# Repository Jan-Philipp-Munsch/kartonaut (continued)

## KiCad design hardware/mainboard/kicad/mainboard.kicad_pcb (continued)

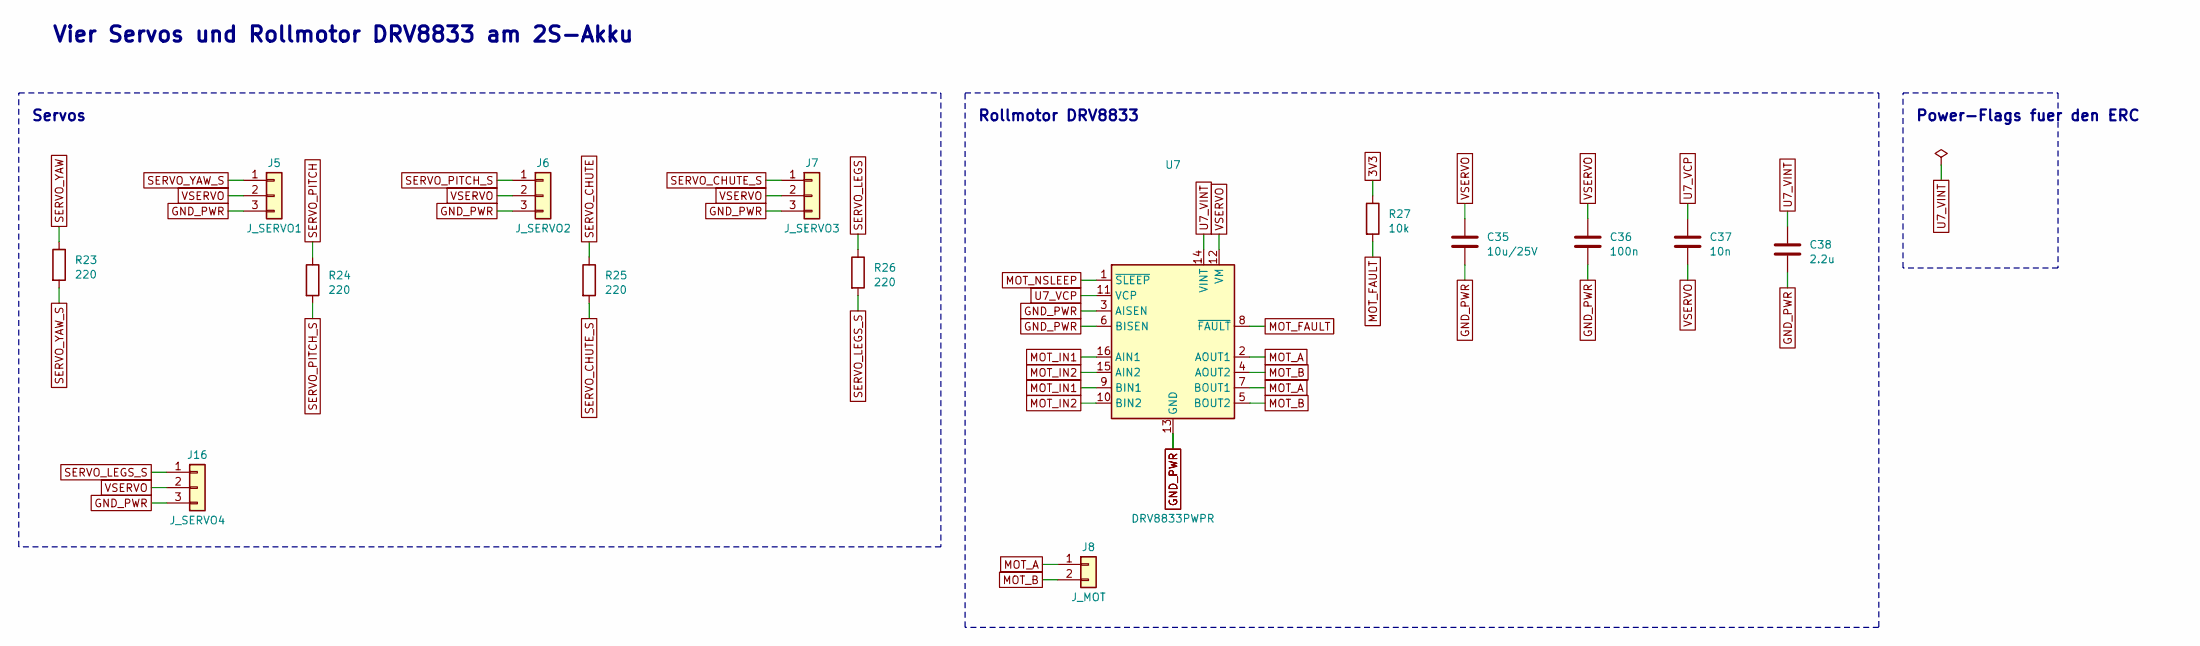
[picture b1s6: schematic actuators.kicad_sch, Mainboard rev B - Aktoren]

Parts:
C35: 10u/25V; C_0805_2012Metric
C36: 100n; C_0603_1608Metric
C37: 10n; C_0603_1608Metric
C38: 2.2u; C_0603_1608Metric
J5: J_SERVO1; JST_XH_S3B-XH-A_1x03_P2.50mm_Horizontal
J6: J_SERVO2; JST_XH_S3B-XH-A_1x03_P2.50mm_Horizontal
J7: J_SERVO3; JST_XH_B3B-XH-A_1x03_P2.50mm_Vertical
J8: J_MOT; JST_XH_B2B-XH-A_1x02_P2.50mm_Vertical
J16: J_SERVO4; JST_XH_B3B-XH-A_1x03_P2.50mm_Vertical
R23, R24, R25, R26: 220; R_0603_1608Metric
R27: 10k; R_0603_1608Metric
U7: DRV8833PWPR; HTSSOP-16-1EP_4.4x5mm_P0.65mm_EP3.4x5mm_Mask2.46x2.31mm_The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; LCSC C50506

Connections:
3V3: R27.1; also elsewhere on the board
GND_PWR: C35.2, C36.2, C38.2, J5.3, J6.3, J7.3, J16.3, U7.3 (AISEN), U7.6 (BISEN), U7.13 (GND), U7.17 (GND); also elsewhere on the board
MOT_A: J8.1, U7.2 (AOUT1), U7.7 (BOUT1)
MOT_B: J8.2, U7.4 (AOUT2), U7.5 (BOUT2)
MOT_FAULT: R27.2, U7.8 (~FAULT); also elsewhere on the board
MOT_IN1: U7.9 (BIN1), U7.16 (AIN1); also elsewhere on the board
MOT_IN2: U7.10 (BIN2), U7.15 (AIN2); also elsewhere on the board
MOT_NSLEEP: U7.1 (~SLEEP); also elsewhere on the board
SERVO_CHUTE: R25.1; also elsewhere on the board
SERVO_CHUTE_S: J7.1, R25.2
SERVO_LEGS: R26.1; also elsewhere on the board
SERVO_LEGS_S: J16.1, R26.2
SERVO_PITCH: R24.1; also elsewhere on the board
SERVO_PITCH_S: J6.1, R24.2
SERVO_YAW: R23.1; also elsewhere on the board
SERVO_YAW_S: J5.1, R23.2
U7_VCP: C37.1, U7.11 (VCP)
U7_VINT: C38.1, U7.14 (VINT)
VSERVO: C35.1, C36.1, C37.2, J5.2, J6.2, J7.2, J16.2, U7.12 (VM); also elsewhere on the board

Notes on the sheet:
Vier Servos und Rollmotor DRV8833 am 2S-Akku
Servos
Rollmotor DRV8833
Power-Flags fuer den ERC

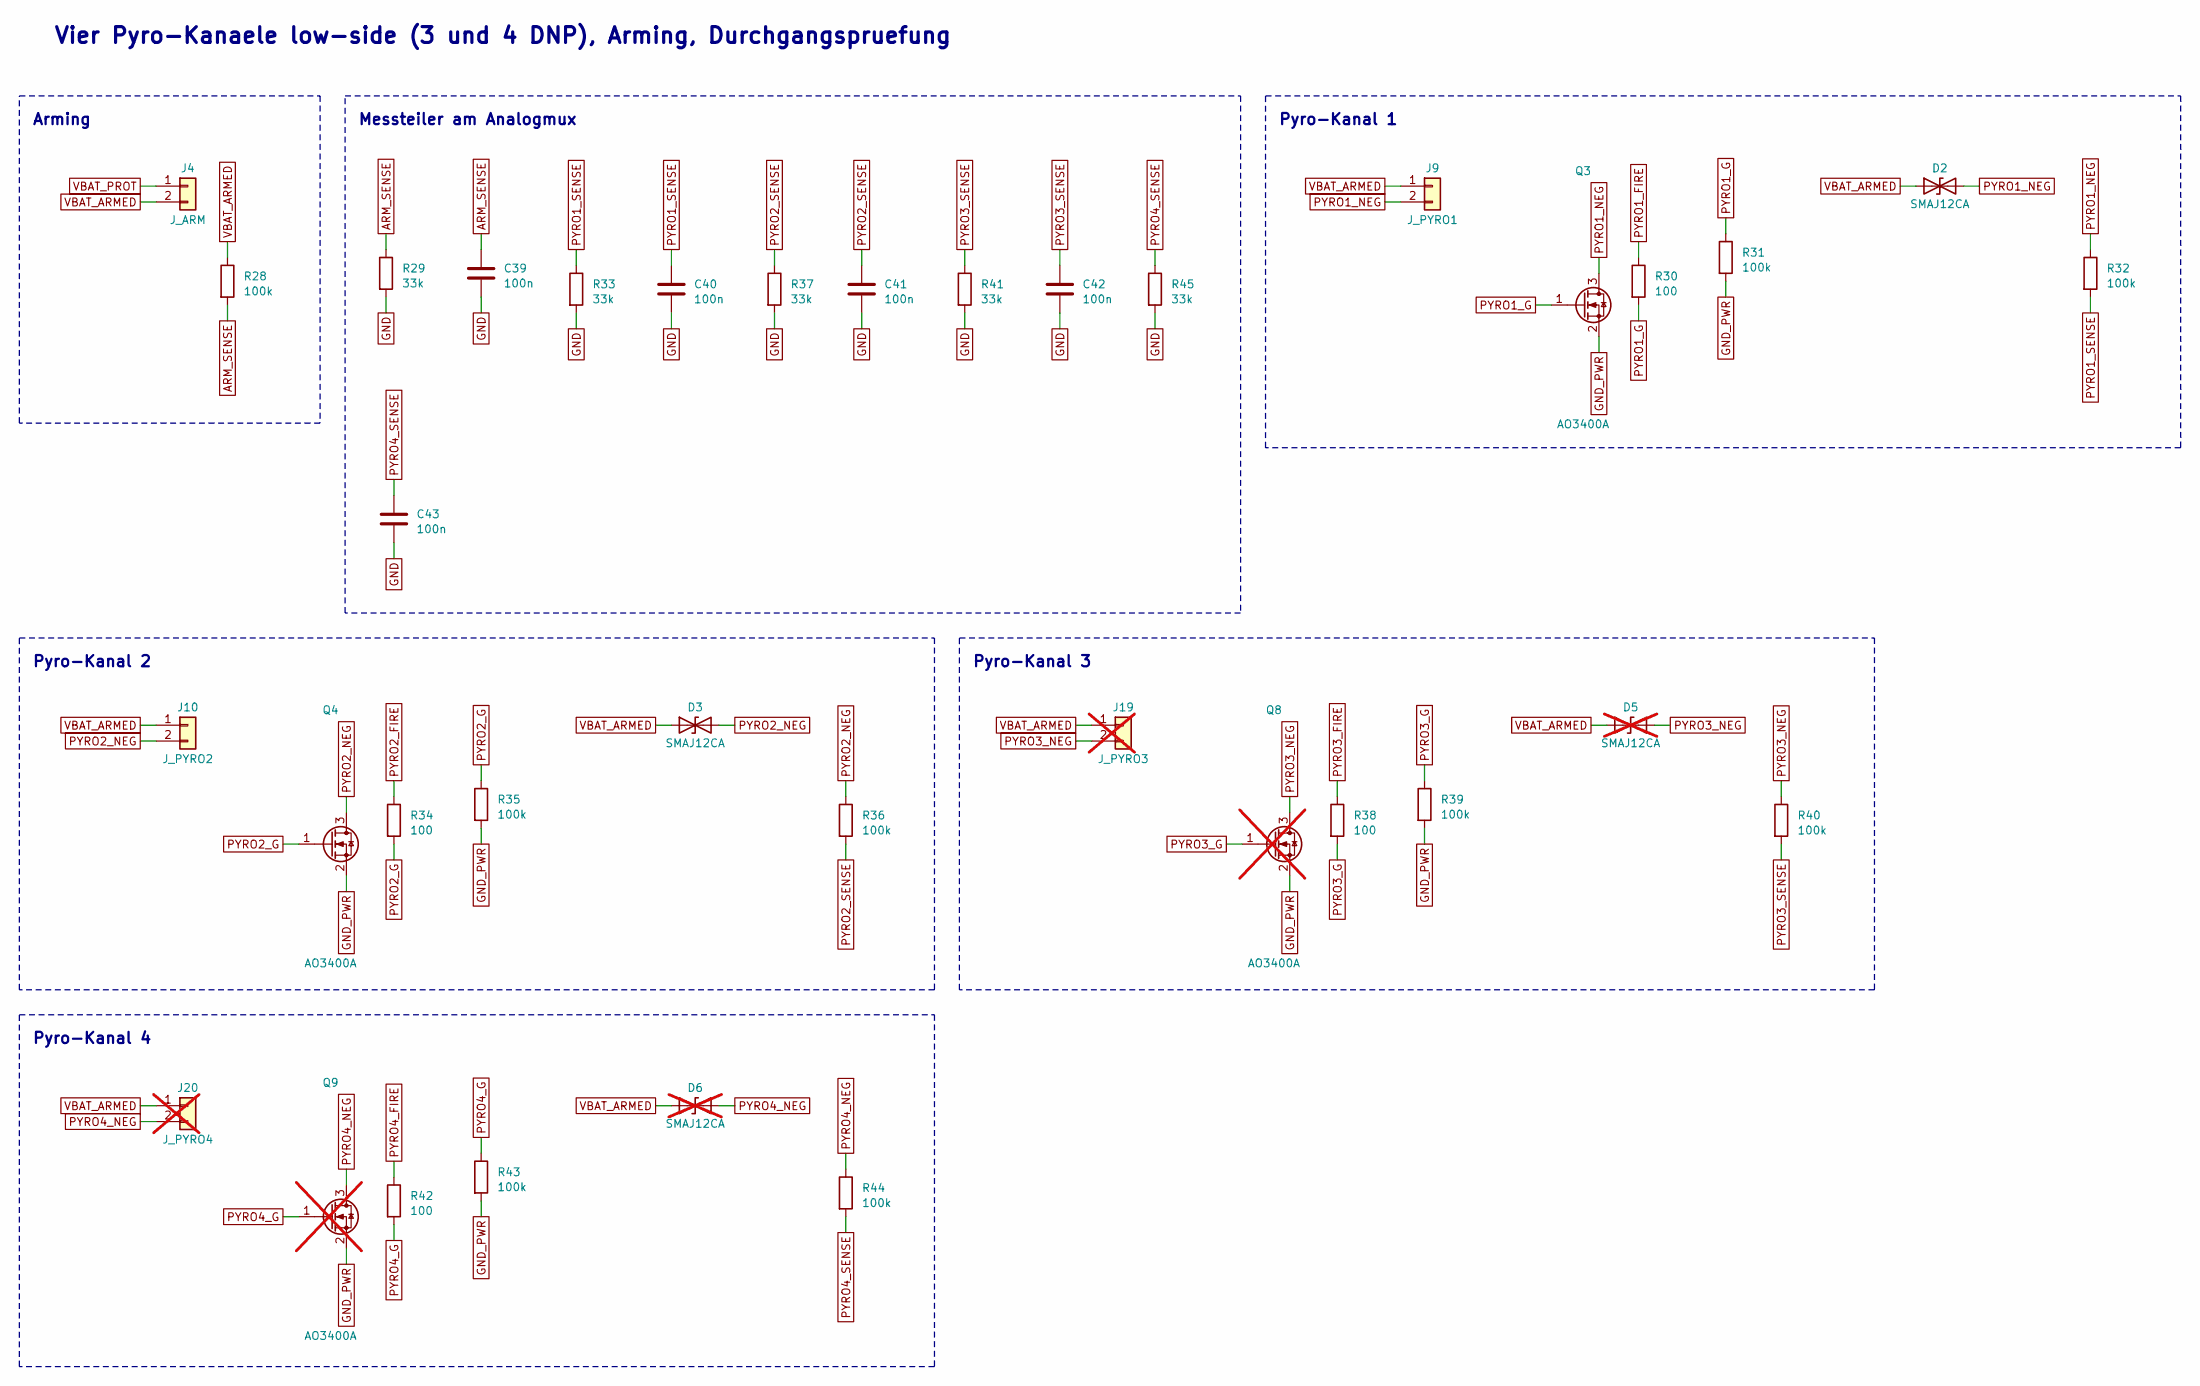
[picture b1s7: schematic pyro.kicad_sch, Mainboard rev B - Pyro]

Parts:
C39, C40, C41, C42, C43: 100n; C_0603_1608Metric
D2, D3: SMAJ12CA; D_SMA
D5, D6: SMAJ12CA; D_SMA; not fitted
J4: J_ARM; JST_XH_B2B-XH-A_1x02_P2.50mm_Vertical
J9: J_PYRO1; JST_XH_S2B-XH-A_1x02_P2.50mm_Horizontal
J10: J_PYRO2; JST_XH_S2B-XH-A_1x02_P2.50mm_Horizontal
J19: J_PYRO3; JST_XH_S2B-XH-A_1x02_P2.50mm_Horizontal; not fitted
J20: J_PYRO4; JST_XH_S2B-XH-A_1x02_P2.50mm_Horizontal; not fitted
Q3, Q4: AO3400A; SOT-23; LCSC C20917
Q8, Q9: AO3400A; SOT-23; LCSC C20917; not fitted
R28, R31, R32, R35, R36, R39, R40, R43, R44: 100k; R_0603_1608Metric
R29, R33, R37, R41, R45: 33k; R_0603_1608Metric
R30, R34, R38, R42: 100; R_0603_1608Metric

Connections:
ARM_SENSE: C39.1, R28.2, R29.1; also elsewhere on the board
GND: C39.2, C40.2, C41.2, C42.2, C43.2, R29.2, R33.2, R37.2, R41.2, R45.2; also elsewhere on the board
GND_PWR: Q3.2 (S), Q4.2 (S), Q8.2 (S), Q9.2 (S), R31.2, R35.2, R39.2, R43.2; also elsewhere on the board
PYRO1_FIRE: R30.1; also elsewhere on the board
PYRO1_G: Q3.1 (G), R30.2, R31.1
PYRO1_NEG: D2.2 (A2), J9.2, Q3.3 (D), R32.1
PYRO1_SENSE: C40.1, R32.2, R33.1; also elsewhere on the board
PYRO2_FIRE: R34.1; also elsewhere on the board
PYRO2_G: Q4.1 (G), R34.2, R35.1
PYRO2_NEG: D3.2 (A2), J10.2, Q4.3 (D), R36.1
PYRO2_SENSE: C41.1, R36.2, R37.1; also elsewhere on the board
PYRO3_FIRE: R38.1; also elsewhere on the board
PYRO3_G: Q8.1 (G), R38.2, R39.1
PYRO3_NEG: D5.2 (A2), J19.2, Q8.3 (D), R40.1
PYRO3_SENSE: C42.1, R40.2, R41.1; also elsewhere on the board
PYRO4_FIRE: R42.1; also elsewhere on the board
PYRO4_G: Q9.1 (G), R42.2, R43.1
PYRO4_NEG: D6.2 (A2), J20.2, Q9.3 (D), R44.1
PYRO4_SENSE: C43.1, R44.2, R45.1; also elsewhere on the board
VBAT_ARMED: D2.1 (A1), D3.1 (A1), D5.1 (A1), D6.1 (A1), J4.2, J9.1, J10.1, J19.1, J20.1, R28.1
VBAT_PROT: J4.1; also elsewhere on the board

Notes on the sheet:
Vier Pyro-Kanaele low-side (3 und 4 DNP), Arming, Durchgangspruefung
Arming
Messteiler am Analogmux
Pyro-Kanal 1
Pyro-Kanal 2
Pyro-Kanal 3
Pyro-Kanal 4

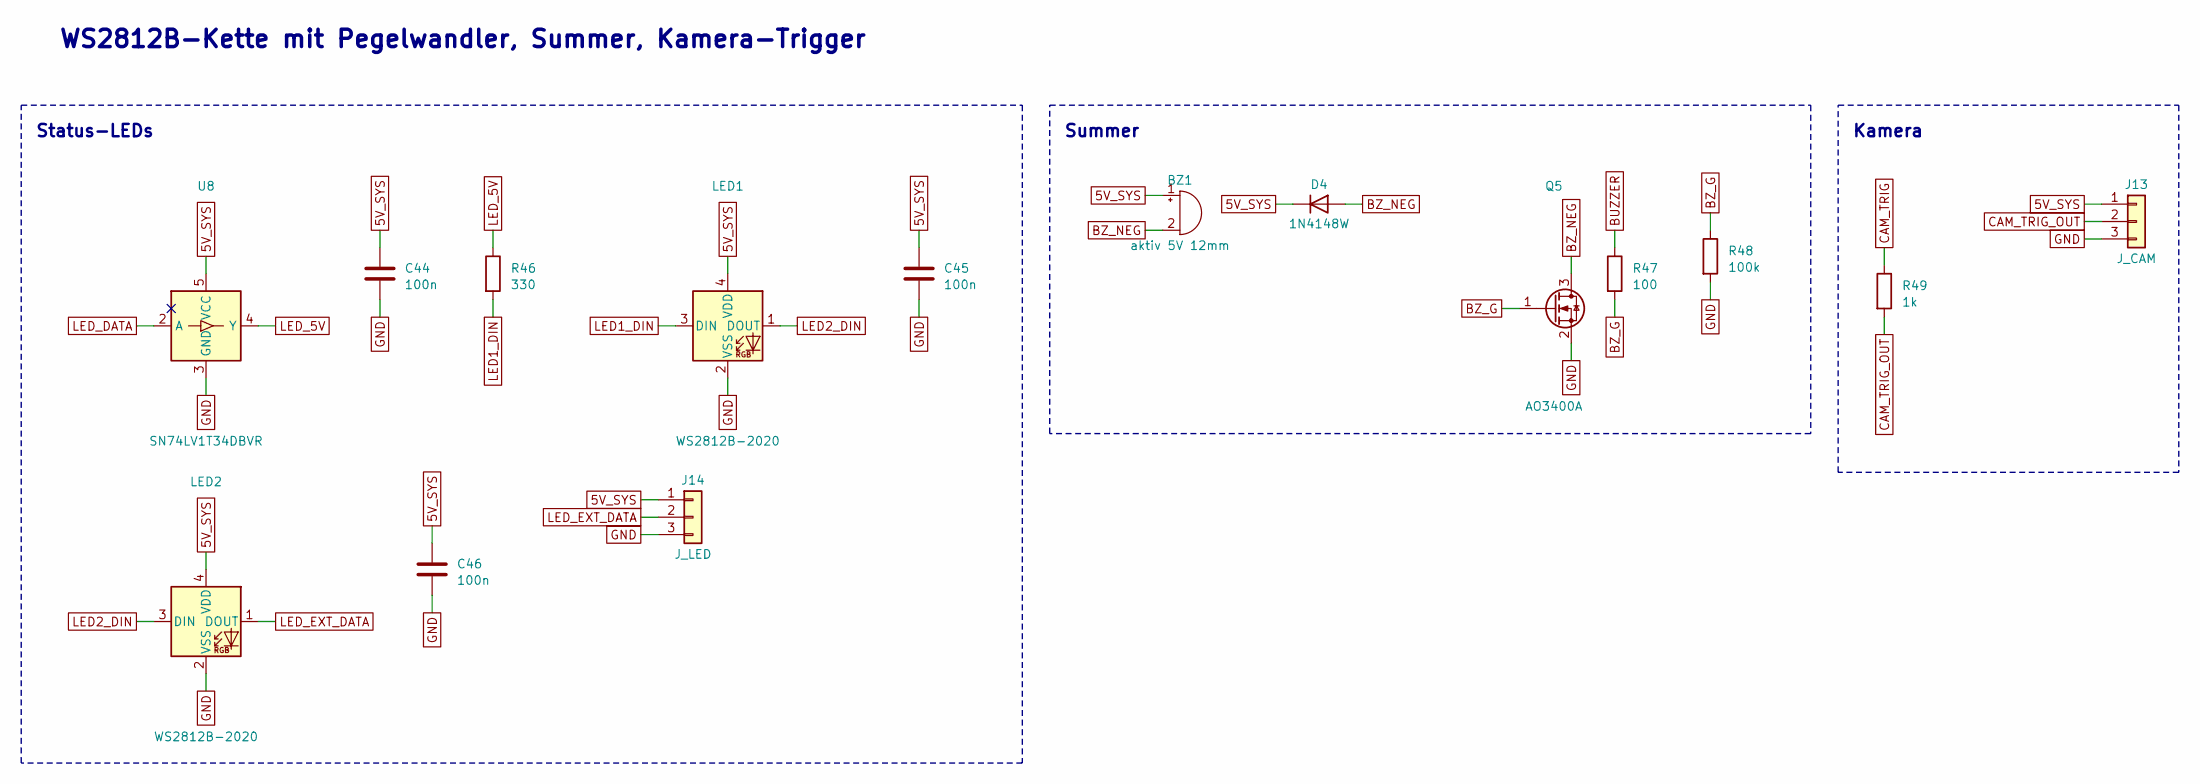
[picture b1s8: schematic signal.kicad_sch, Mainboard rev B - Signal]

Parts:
BZ1: aktiv 5V 12mm; Buzzer_12x9.5RM7.6
C44, C45, C46: 100n; C_0603_1608Metric
D4: 1N4148W; D_SOD-123; LCSC C81598
J13: J_CAM; JST_GH_BM03B-GHS-TBT_1x03-1MP_P1.25mm_Vertical
J14: J_LED; JST_GH_BM03B-GHS-TBT_1x03-1MP_P1.25mm_Vertical
LED1, LED2: WS2812B-2020; LED_WS2812B-2020_PLCC4_2.0x2.0mm; LCSC C965555
Q5: AO3400A; SOT-23; LCSC C20917
R46: 330; R_0603_1608Metric
R47: 100; R_0603_1608Metric
R48: 100k; R_0603_1608Metric
R49: 1k; R_0603_1608Metric
U8: SN74LV1T34DBVR; SOT-23-5

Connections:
5V_SYS: BZ1.1 (+), C44.1, C45.1, C46.1, D4.1 (K), J13.1, J14.1, LED1.4 (VDD), LED2.4 (VDD), U8.5 (VCC); also elsewhere on the board
BUZZER: R47.1; also elsewhere on the board
BZ_G: Q5.1 (G), R47.2, R48.1
BZ_NEG: BZ1.2 (-), D4.2 (A), Q5.3 (D)
CAM_TRIG: R49.1; also elsewhere on the board
CAM_TRIG_OUT: J13.2, R49.2
GND: C44.2, C45.2, C46.2, J13.3, J14.3, LED1.2 (VSS), LED2.2 (VSS), Q5.2 (S), R48.2, U8.3 (GND); also elsewhere on the board
LED1_DIN: LED1.3 (DIN), R46.2
LED2_DIN: LED1.1 (DOUT), LED2.3 (DIN)
LED_5V: R46.1, U8.4 (Y)
LED_DATA: U8.2 (A); also elsewhere on the board
LED_EXT_DATA: J14.2, LED2.1 (DOUT)

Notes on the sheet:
WS2812B-Kette mit Pegelwandler, Summer, Kamera-Trigger
Status-LEDs
Summer
Kamera

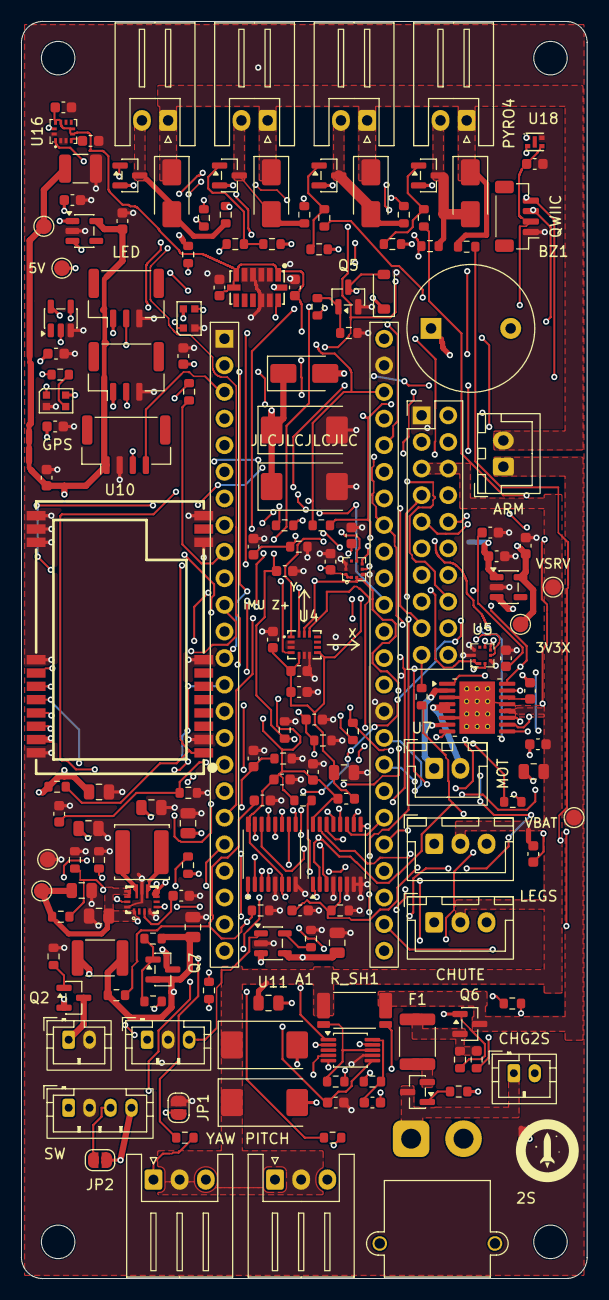
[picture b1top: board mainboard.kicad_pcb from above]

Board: 4 copper layers, 54.0 x 120.0 mm, 174 parts (0 on the bottom side), 117 nets.

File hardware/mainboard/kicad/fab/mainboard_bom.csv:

Comment,Designator,Footprint,LCSC Part #
100n,"C1,C2,C3,C7,C12,C24,C25,C26,C29,C30,C34,C36,C39,C40,C41,C42,C43,C44,C45,C46,C47,C48,C49",C_0603_1608Metric,
330u/16V polymer,"C4,C5",CP_EIA-7343-31_Kemet-D,
10u/25V,"C6,C10,C11,C35",C_0805_2012Metric,
4.7u,"C8,C9",C_0805_2012Metric,
22u/10V,"C13,C14,C15",C_0805_2012Metric,
470u/6.3V polymer,"C16,C17",CP_EIA-7343-31_Kemet-D,
1u,"C18,C19,C21,C22",C_0603_1608Metric,
100u/6.3V,C20,C_1210_3225Metric,
10u,"C23,C33",C_0805_2012Metric,
2.2u,"C27,C38",C_0603_1608Metric,
10n,"C28,C37",C_0603_1608Metric,
SS14,D1,D_SMA,C2480
SMAJ12CA,"D2,D3",D_SMA,
1N4148W,D4,D_SOD-123,C81598
3A hold 6A trip,F1,Fuse_1812_4532Metric,
2A hold,F2,Fuse_1812_4532Metric,
600R@100MHz,FB1,L_0603_1608Metric,
J_GPS,J11,JST_GH_BM04B-GHS-TBT_1x04-1MP_P1.25mm_Vertical,
J_QWIIC,J12,JST_SH_BM04B-SRSS-TB_1x04-1MP_P1.00mm_Vertical,
J_CAM,J13,JST_GH_BM03B-GHS-TBT_1x03-1MP_P1.25mm_Vertical,
J_LED,J14,JST_GH_BM03B-GHS-TBT_1x03-1MP_P1.25mm_Vertical,
1.5u Isat>=4A,L2,L_Changjiang_FNR5040S,
WS2812B-2020,"LED1,LED2",LED_WS2812B-2020_PLCC4_2.0x2.0mm,C965555
AO3401A,"Q1,Q2,Q6,Q7",SOT-23,C15127
AO3400A,"Q3,Q4,Q5",SOT-23,C20917
10k,"R1,R8,R18,R19,R22,R27",R_0603_1608Metric,
100k,"R2,R4,R9,R11,R28,R31,R32,R35,R36,R39,R40,R43,R44,R48",R_0603_1608Metric,
1k,"R3,R10,R49",R_0603_1608Metric,
33k,"R5,R12,R29,R33,R37,R41,R45",R_0603_1608Metric,
10,"R6,R7",R_0603_1608Metric,
2k,R13,R_0603_1608Metric,
680k,R14,R_0603_1608Metric,
130k,R15,R_0603_1608Metric,
330k,R16,R_0603_1608Metric,
115k,R17,R_0603_1608Metric,
4.7k,"R20,R21",R_0603_1608Metric,
220,"R23,R24,R25,R26",R_0603_1608Metric,
100,"R30,R34,R38,R42,R47",R_0603_1608Metric,
330,R46,R_0603_1608Metric,
20m 1% 1W,R_SH1,R_2512_Kelvin,
TPS63070RNMR,U2,VQFN-15_L3.0-W2.5-P0.50-BL,C109322
AP2112K-3.3TRG1,"U3,U14",SOT-23-5,C51118
LSM6DSV16X,U4,LGA-14_L3.0-W2.5-P0.50-TL,C5267406
BMP390,U5,LGA-10_L2.0-W2.0-P0.50-BL,C5124834
INA239AIDGSR,U6,MSOP-10_3x3mm_P0.5mm,
DRV8833PWPR,U7,HTSSOP-16-1EP_4.4x5mm_P0.65mm_EP3.4x5mm_Mask2.46x2.31mm_ThermalVias,C50506
SN74LV1T34DBVR,U8,SOT-23-5,
E22-400T22S,U10,WIRELM-SMD_E22-400T22S_1,C2903765
MCP73831T-2ACI/OT,U11,SOT-23-5,C424093
74HC138PW,U12,TSSOP-16_4.4x5mm_P0.65mm,
74HC4051PW,U13,TSSOP-16_4.4x5mm_P0.65mm,
LIS3MDL,U16,LGA-12_L2.0-W2.0-P0.50-BL,C478483
SHT40-AD1B,U18,DFN-4_L1.5-W1.5-P0.8-TL-EP,C2848306

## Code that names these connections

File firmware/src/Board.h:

#pragma once
// Board.h – Welche Hardware trägt die Flug-Firmware?
//
// Zwei Rückenden, gewählt über die Build-Variable BOARD_REVB (platformio.ini):
//
//   (ohne)       Breakouts am Teensy 4.1 mit Dupont-Kabeln: ICM-20948 (I²C, DMP),
//                BMP280, INA219, HC-12 an Serial8, zwei WS2812B an Pin 5 und 6.
//                Pins wie bisher in Config.h.
//   BOARD_REVB   Mainboard rev B: ICM-42688-P, BMP390, INA239 an SPI1 über den
//                CS-Decoder, Akkus/ARM/Pyro-Durchgang über die Analogmux, LoRa
//                E22 an Serial8, LED-Kette an Pin 5. Pins aus lib/mainboard_revb/
//                BoardRevB.h, geprüft durch firmware/tools/check_board_pins.py.
//
// Die Module (Sensors, Control, Indicators, Radio, Pyro-Ausgänge) lesen Pins
// nur von hier. Config.h hält Physik, Gewinne und Schalter, nichts Elektrisches.
#include <Arduino.h>
#include "MathTypes.h"

#ifdef BOARD_REVB
  #include "BoardRevB.h"
  #define BOARD_NAME "Mainboard rev B"

  constexpr int PIN_BEEPER      = revb::PIN_BUZZER;       // 37
  constexpr int PIN_LED_DATA    = revb::PIN_LED_DATA;     // 5, Kette LED1 -> LED2 -> J_LED
  constexpr int LED_COUNT       = revb::LED_COUNT_ONBOARD;
  constexpr int PIN_MOT_IN1     = revb::PIN_MOT_IN1;
  constexpr int PIN_MOT_IN2     = revb::PIN_MOT_IN2;
  constexpr int PIN_MOT_NSLEEP  = revb::PIN_MOT_NSLEEP;   // DRV8833, tief = Motor stromlos
  constexpr int PIN_MOT_FAULT   = revb::PIN_MOT_FAULT;
  constexpr int PIN_SERVO_YAW   = revb::PIN_SERVO_YAW;
  constexpr int PIN_SERVO_PITCH = revb::PIN_SERVO_PITCH;
  constexpr int PIN_SERVO_CHUTE = revb::PIN_SERVO_CHUTE;
  constexpr int PIN_SERVO_LEGS  = revb::PIN_SERVO_LEGS;
  constexpr int PIN_PYRO_FIRE[4] = {revb::PIN_PYRO1_FIRE, revb::PIN_PYRO2_FIRE, revb::PIN_PYRO3_FIRE, revb::PIN_PYRO4_FIRE};
  constexpr bool PYRO_FITTED[4]  = {revb::PYRO_FITTED[0], revb::PYRO_FITTED[1], revb::PYRO_FITTED[2], revb::PYRO_FITTED[3]};
  constexpr int PIN_PYRO1       = revb::PIN_PYRO1_FIRE;
  constexpr int PIN_CAM_TRIG    = revb::PIN_CAM_TRIG;
  constexpr int PIN_THROTTLE    = revb::PIN_PWM_EXT;      // ESC am Prüfstand (J_STACK PWM_EXT)
  constexpr int PIN_LORA_M0     = revb::PIN_LORA_M0;
  constexpr int PIN_LORA_M1     = revb::PIN_LORA_M1;
  constexpr int PIN_LORA_AUX    = revb::PIN_LORA_AUX;
  constexpr int PIN_LORA_NRST   = revb::PIN_LORA_NRST;
  constexpr bool HAS_ARM_SENSE   = true;    // Schlüsselschalter messbar
  constexpr bool HAS_PYRO_SENSE  = true;    // Durchgang je Kanal messbar
  constexpr bool HAS_VBAT_SENSE  = true;    // beide Akkus am ADC
  constexpr bool HAS_GPS         = true;    // J_GPS an Serial1
  constexpr bool RADIO_IS_E22    = true;

  // Drehung Chip -> Körpersystem (x, y quer, z Rollachse zur Spitze).
  // Spezifikation rev B §2: Chip X zeigt quer (+u), Chip Y zur Spitze (+v),
  // also Körper = (c.x, -c.z, c.y). TODO: nach der endgültigen Platzierung von
  // U4 (Bestückungsdruck-Pfeile) am Gerät prüfen: Spitze nach oben -> a.z ≈ +9,81.
  inline Vec3 chipToBody(const Vec3& c) { return Vec3(c.x, -c.z, c.y); }

#else
  #define BOARD_NAME "Breakouts (Teensy 4.1, I2C)"

  constexpr int PIN_BEEPER      = 13;
  constexpr int PIN_LED1        = 5;    // WS2812B, einzeln
  constexpr int PIN_LED2        = 6;
  constexpr int LED_COUNT       = 2;
  constexpr int PIN_MOT_IN1     = 2;    // Rollmotor, H-Brücke
  constexpr int PIN_MOT_IN2     = 3;
  constexpr int PIN_MOT_NSLEEP  = -1;   // nicht vorhanden
  constexpr int PIN_MOT_FAULT   = -1;
  constexpr int PIN_SERVO_YAW   = 28;   // TVC
  constexpr int PIN_SERVO_PITCH = 29;
  constexpr int PIN_SERVO_CHUTE = 9;    // Fallschirm (Servo, Reserve)
  constexpr int PIN_SERVO_LEGS  = -1;
  constexpr int PIN_PYRO_FIRE[4] = {23, 22, -1, -1};   // Low-Side-MOSFET-Modul an 23 (Pyro-Test)
  constexpr bool PYRO_FITTED[4]  = {true, false, false, false};
  constexpr int PIN_PYRO1       = 23;
  constexpr int PIN_CAM_TRIG    = -1;
  constexpr int PIN_THROTTLE    = 10;   // ESC am Prüfstand, freier PWM-Pin
  constexpr int PIN_LORA_M0     = -1;   // HC-12: SET-Pin nicht benutzt
  constexpr int PIN_LORA_M1     = -1;
  constexpr int PIN_LORA_AUX    = -1;
  constexpr int PIN_LORA_NRST   = -1;
  constexpr bool HAS_ARM_SENSE   = false;
  constexpr bool HAS_PYRO_SENSE  = false;
  constexpr bool HAS_VBAT_SENSE  = false;
  constexpr bool HAS_GPS         = false;
  constexpr bool RADIO_IS_E22    = false;

  constexpr uint32_t I2C_MAIN_SPEED_HZ = 400000;   // BMP280, INA219, ICM-20948
  // Lage des ICM-20948-Breakouts: wie bisher (Chipachsen = Körperachsen)
  inline Vec3 chipToBody(const Vec3& c) { return c; }
#endif

// Funk hängt bei beiden an Serial8 (RX8 = 34, TX8 = 35)
#define RADIO_SERIAL Serial8
#define GPS_SERIAL   Serial1

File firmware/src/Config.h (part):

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#ifdef BOARD_REVB
// Mainboard rev B: Pins aus BoardRevB.h; hier nur die Aliase, die die Module benutzen.
constexpr int PIN_BEEPER      = 37;
constexpr int PIN_LED_DATA    = 5;    // WS2812B-Kette LED1 -> LED2
constexpr int PIN_MOT_IN1     = 2;    // DRV8833
constexpr int PIN_MOT_IN2     = 3;
constexpr int PIN_MOT_NSLEEP  = 11;
constexpr int PIN_SERVO_YAW   = 28;
constexpr int PIN_SERVO_PITCH = 29;
constexpr int PIN_SERVO_CHUTE = 9;
constexpr int PIN_PYRO1       = 23;
constexpr int PIN_PYRO2       = 22;
constexpr int PIN_RADIO_M0    = 33;   // E22: M0 = M1 = 0 -> transparenter Modus
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constexpr int PIN_BEEPER      = 13;
constexpr int PIN_LED1        = 5;    // WS2812B
constexpr int PIN_LED2        = 6;    // WS2812B
constexpr int PIN_MOT_IN1     = 2;    // Rollmotor, H-Brücke
constexpr int PIN_MOT_IN2     = 3;
constexpr int PIN_SERVO_YAW   = 28;   // TVC
constexpr int PIN_SERVO_PITCH = 29;   // TVC
constexpr int PIN_SERVO_CHUTE = 9;    // Fallschirm
constexpr int PIN_PYRO1       = 23;   // Low-Side-MOSFET, Mainboard rev A: PYRO1_FIRE
constexpr int PIN_PYRO2       = -1;   // nicht vorhanden
#endif
// Funk hängt an Serial8 (RX8 = 34, TX8 = 35): HC-12 heute, E22 auf rev B
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constexpr bool     THROTTLE_ENABLED      = false;    // erst mit Drosselmechanik und Experiment E05
constexpr float    THROTTLE_F_MIN        = 0.5f;     // Axialschub bei ganz eingeschwenkten Pads (Kennlinie E05)
#ifdef BOARD_REVB
constexpr int      PIN_SERVO_THROTTLE    = 10;       // J_SERVO4 (SERVO_LEGS) an VSERVO, solange die Beine keinen Servo haben
#else
constexpr int      PIN_SERVO_THROTTLE    = -1;       // Breakouts: kein freier Servoausgang
#endif
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constexpr uint32_t PYRO_BACKUP_DELAY_MS = 1500;    // Kanal 2 zündet so viel später, falls bestückt
constexpr uint32_t PYRO_RETRY_DELAY_MS  = 500;     // zweiter Versuch, wenn der Durchgang nach dem Puls bleibt
constexpr uint8_t  PYRO_MAX_FIRES       = 2;       // Versuche je Kanal
constexpr float    PYRO_ARM_MIN_V       = 5.0f;    // ARM_SENSE darüber = scharf (2S hinter dem Schlüssel)
constexpr float    PYRO_CONT_MIN_RATIO  = 0.8f;    // Durchgang: PYRO_SENSE > Ratio · ARM

// ===== Telemetrie (Telemetry.h) =====
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
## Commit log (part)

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2025-10-12 test
2025-10-12 test 2
2025-10-13 sd_logger, flash fail
2025-10-13 kalman filter optimization
2025-10-14 csv format problems
2025-10-14 Code Umstrukturierung
2025-10-14 ordner noch trennen!
2025-10-14 Logger Implementation
2025-10-14 loop time problems
2025-10-20 Gyro integration and radio test
2025-10-20 Controls under control
2025-10-26 26.10
2025-10-26 deleted groundcode
